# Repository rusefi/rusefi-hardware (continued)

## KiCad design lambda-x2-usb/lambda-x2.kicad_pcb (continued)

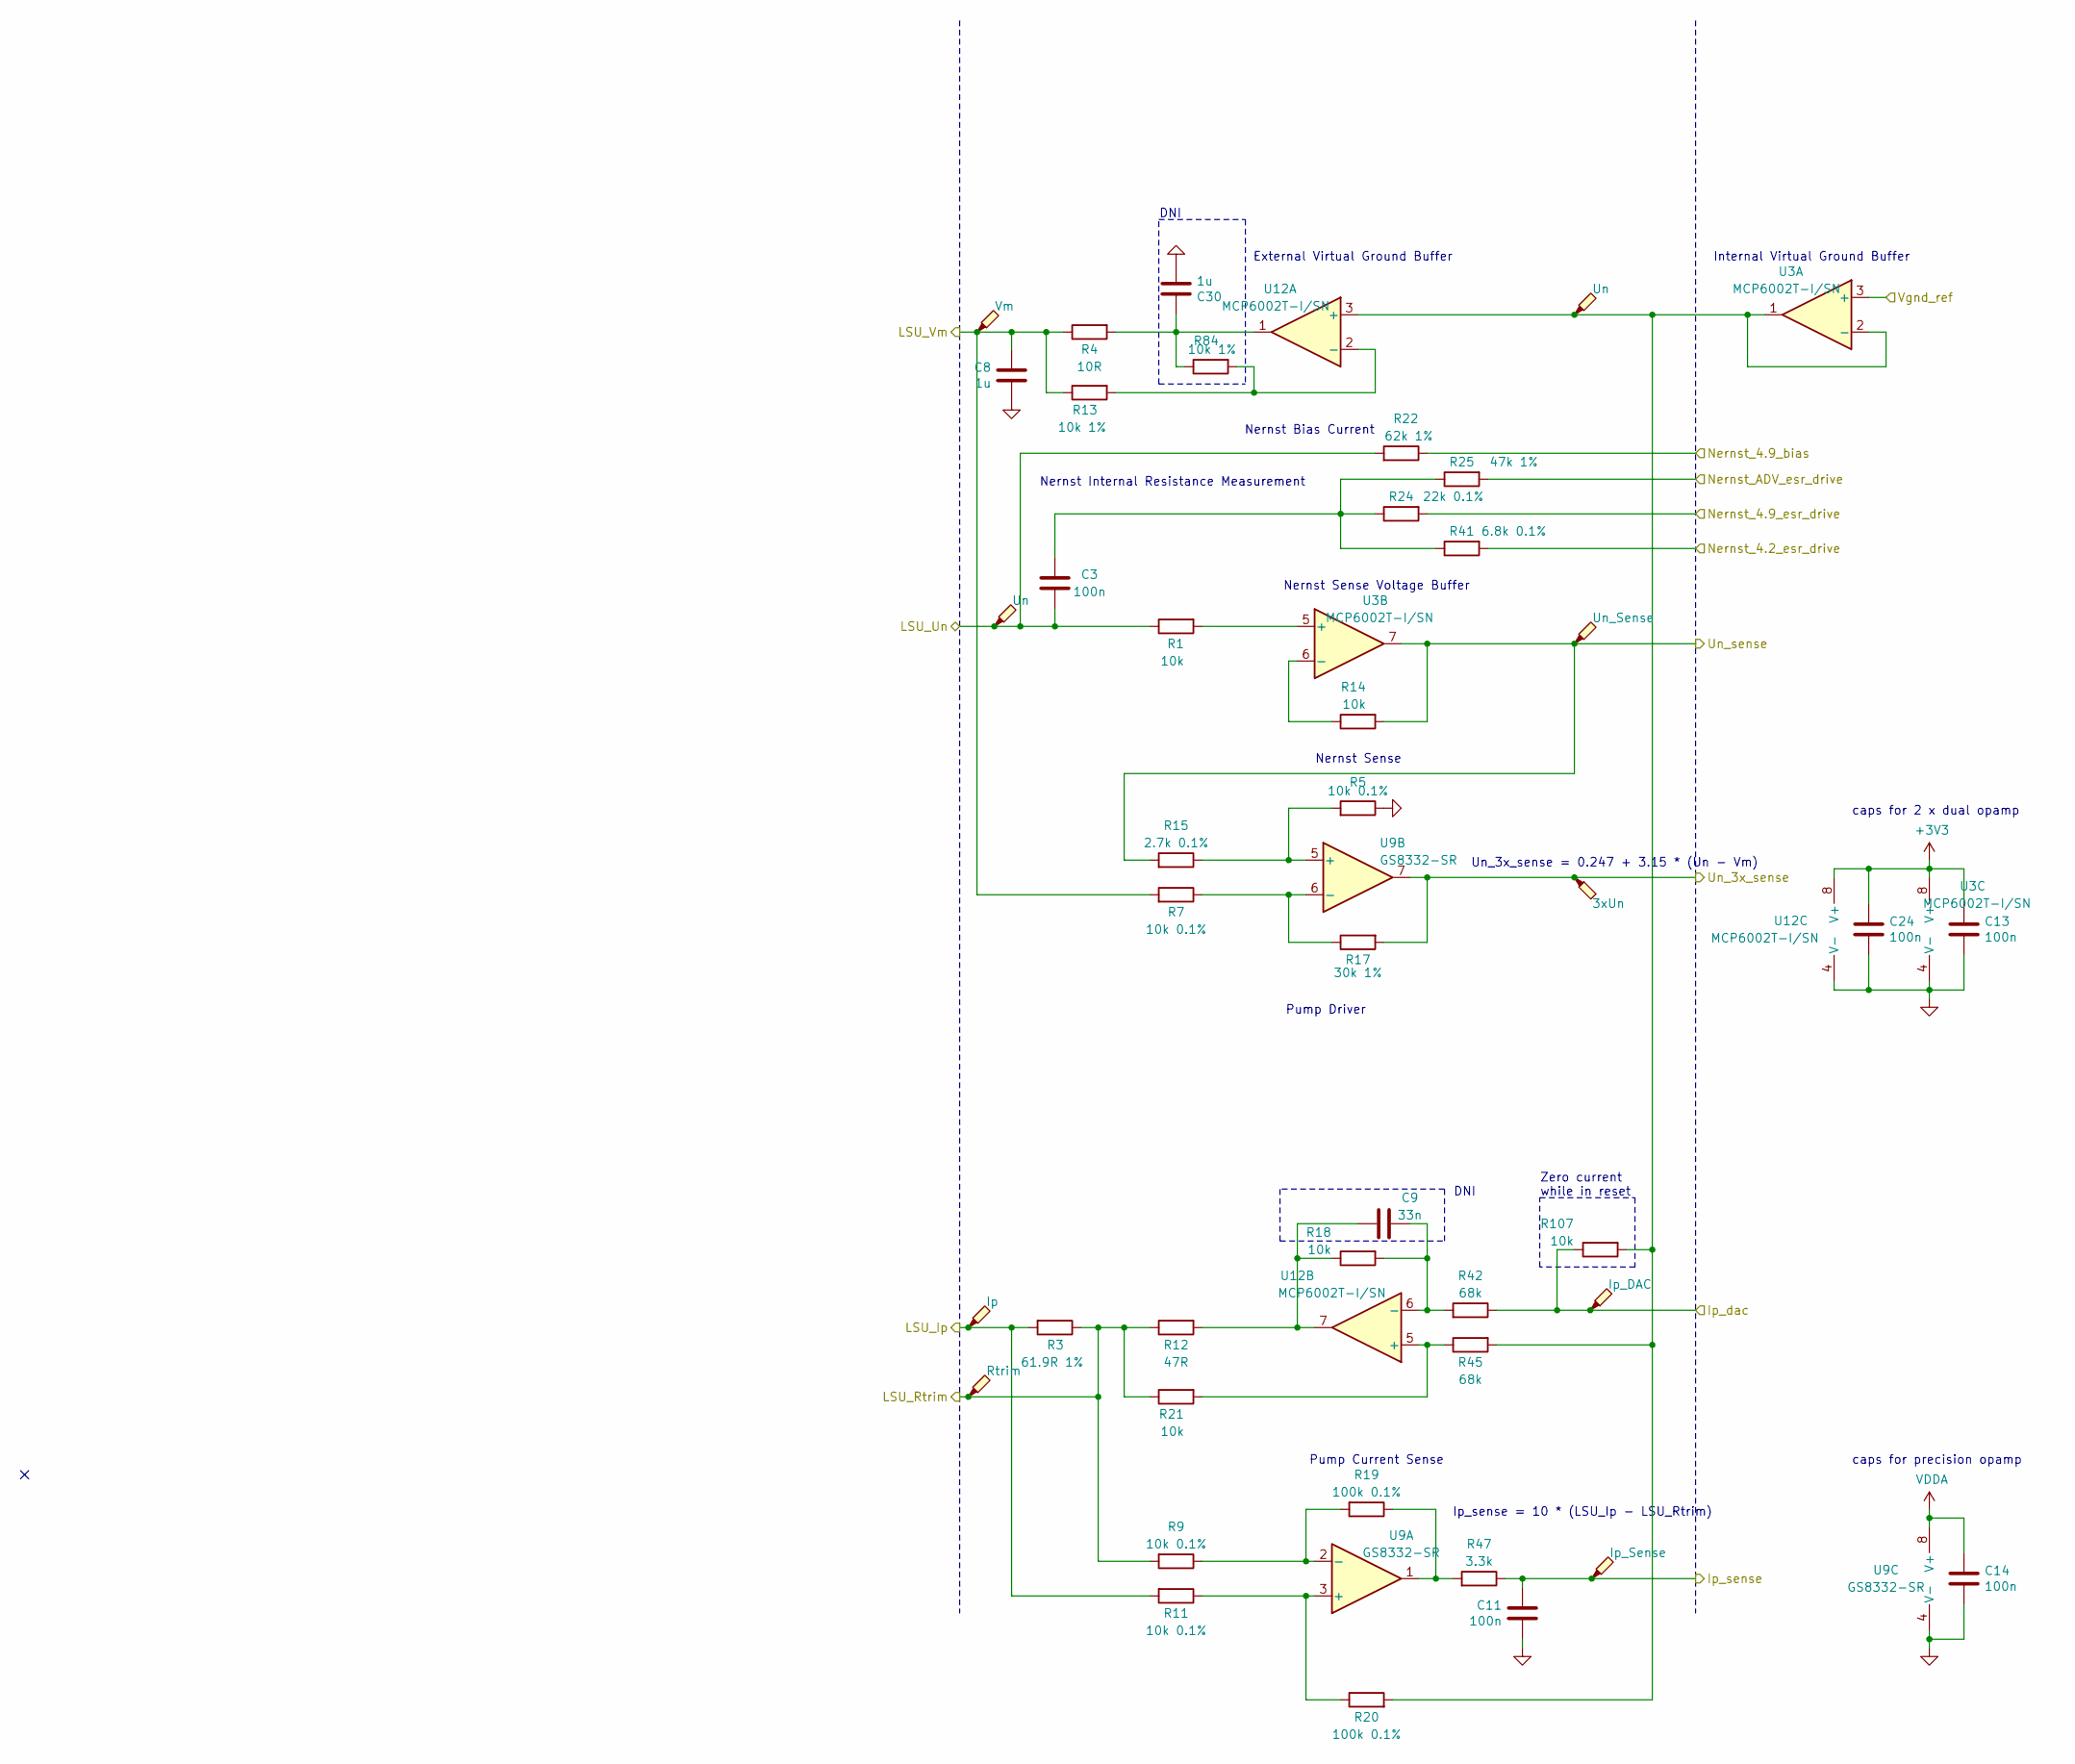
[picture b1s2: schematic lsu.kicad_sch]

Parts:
C3, C11, C13, C14, C24: 100n; C_0402_1005Metric; LCSC C1525
C8, C30: 1u; C_0402_1005Metric; LCSC C52923
C9: 33n; C_0402_1005Metric; LCSC C1585
R1, R14, R18, R21, R107: 10k; R_0402_1005Metric; LCSC C25744
R3: 61.9R 1%; R_0805_2012Metric; LCSC C322537
R4: 10R; R_1206_3216Metric; LCSC C17903
R5, R7, R9, R11: 10k 0.1%; R_0603_1608Metric; LCSC C309083
R12: 47R; R_0603_1608Metric; LCSC C328363
R13, R84: 10k 1%; R_0402_1005Metric; LCSC C25744
R15: 2.7k 0.1%; R_0603_1608Metric; LCSC C318131
R17: 30k 1%; R_0603_1608Metric; LCSC C22984
R19, R20: 100k 0.1%; R_0603_1608Metric; LCSC C122538
R22: 62k 1%; R_0603_1608Metric; LCSC C23221
R24: 22k 0.1%; R_0603_1608Metric; LCSC C705830
R25: 47k 1%; R_0603_1608Metric; LCSC C25819
R41: 6.8k 0.1%; R_0603_1608Metric; LCSC C705876
R42, R45: 68k; R_0402_1005Metric; LCSC C36871
R47: 3.3k; R_0402_1005Metric; LCSC C25890
TP3: Un_Sense; TestPoint_Pad_D1.0mm
TP5: 3xUn; TestPoint_Pad_D1.0mm
TP10: Ip; TestPoint_Pad_D1.0mm
TP11: Rtrim; TestPoint_Pad_D1.0mm
TP12: Vm; TestPoint_Pad_D1.0mm
TP13, TP14: Un; TestPoint_Pad_D1.0mm
TP15: Ip_DAC; TestPoint_Pad_D1.0mm
TP16: Ip_Sense; TestPoint_Pad_D1.0mm
U3, U12: MCP6002T-I/SN; SOIC-8_3.9x4.9mm_P1.27mm; LCSC C7377
U9: GS8332-SR; SOIC-8_3.9x4.9mm_P1.27mm; LCSC C157713

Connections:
+3V3: C13.1, C24.1, U3.8 (V+), U12.8 (V+); also elsewhere on the board
/LSU analog left/Un_sense: R14.2, R15.2, TP3.1, U3.7; also elsewhere on the board
/LSU analog left/Vgnd_ref: U3.3 (+); also elsewhere on the board
/L_Ip_dac: R42.1, R107.1, TP15.1; also elsewhere on the board
/L_Ip_sense: C11.1, R47.1, TP16.1; also elsewhere on the board
/L_LSU_Ip: R3.2, R11.2, TP10.1; also elsewhere on the board
/L_LSU_Rtrim: R3.1, R9.2, R12.1, R21.1, TP11.1; also elsewhere on the board
/L_LSU_Un: C3.1, R1.1, R22.2, TP13.1; also elsewhere on the board
/L_LSU_Vm: C8.1, R4.1, R7.2, R13.1, TP12.1; also elsewhere on the board
/L_Nernst_4.2_esr_drive: R41.2; also elsewhere on the board
/L_Nernst_4.9_bias: R22.1; also elsewhere on the board
/L_Nernst_4.9_esr_drive: R24.2; also elsewhere on the board
/L_Nernst_ADV_esr_drive: R25.2; also elsewhere on the board
/L_Un_3x_sense: R17.2, TP5.1, U9.7; also elsewhere on the board
GND: C8.2, C11.2, C13.2, C14.2, C24.2, C30.2, R5.1, U3.4 (V-), U9.4 (V-), U12.4 (V-); also elsewhere on the board
unnamed: C3.2, R24.1, R25.1, R41.1
unnamed: C9.1, R12.2, R18.1, U12.7
unnamed: C30.1, R4.2, R84.1, U12.1
unnamed: R19.1, R47.2, U9.1
unnamed: R1.2, U3.5 (+)
unnamed: R14.1, U3.6 (-)
unnamed: R11.1, R20.1, U9.3 (+)
unnamed: R9.1, R19.2, U9.2 (-)
unnamed: R5.2, R15.1, U9.5 (+)
unnamed: R7.1, R17.1, U9.6 (-)
unnamed: R20.2, R45.2, R107.2, TP14.1, U3.1, U3.2 (-), U12.3 (+)
unnamed: R13.2, R84.2, U12.2 (-)
unnamed: R21.2, R45.1, U12.5 (+)
unnamed: C9.2, R18.2, R42.2, U12.6 (-)
VDDA: C14.1, U9.8 (V+); also elsewhere on the board

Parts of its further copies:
C15, C18, C20, C23, C29: 100n; C_0402_1005Metric; LCSC C1525
C16, C31: 1u; C_0402_1005Metric; LCSC C52923
C17: 33n; C_0402_1005Metric; LCSC C1585
R54, R63, R66, R69, R108: 10k; R_0402_1005Metric; LCSC C25744
R55: 61.9R 1%; R_0805_2012Metric; LCSC C322537
R56: 10R; R_1206_3216Metric; LCSC C17903
R57, R58, R59, R60: 10k 0.1%; R_0603_1608Metric; LCSC C309083
R61: 47R; R_0603_1608Metric; LCSC C328363
R62, R85: 10k 1%; R_0402_1005Metric; LCSC C25744
R64: 2.7k 0.1%; R_0603_1608Metric; LCSC C318131
R65: 30k 1%; R_0603_1608Metric; LCSC C22984
R67, R68: 100k 0.1%; R_0603_1608Metric; LCSC C122538
R70: 62k 1%; R_0603_1608Metric; LCSC C23221
R71: 22k 0.1%; R_0603_1608Metric; LCSC C705830
R72: 47k 1%; R_0603_1608Metric; LCSC C25819
R73: 6.8k 0.1%; R_0603_1608Metric; LCSC C705876
R74, R75: 68k; R_0402_1005Metric; LCSC C36871
R77: 3.3k; R_0402_1005Metric; LCSC C25890
TP4: Un_Sense; TestPoint_Pad_D1.0mm
TP6: 3xUn; TestPoint_Pad_D1.0mm
TP17: Ip; TestPoint_Pad_D1.0mm
TP18: Rtrim; TestPoint_Pad_D1.0mm
TP19: Vm; TestPoint_Pad_D1.0mm
TP20, TP21: Un; TestPoint_Pad_D1.0mm
TP22: Ip_DAC; TestPoint_Pad_D1.0mm
TP23: Ip_Sense; TestPoint_Pad_D1.0mm
U10, U13: MCP6002T-I/SN; SOIC-8_3.9x4.9mm_P1.27mm; LCSC C7377
U11: GS8332-SR; SOIC-8_3.9x4.9mm_P1.27mm; LCSC C157713

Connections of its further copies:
+3V3: C20.1, C29.1, U10.8 (V+), U13.8 (V+); also elsewhere on the board
/LSU analog left/Vgnd_ref: U10.3 (+); also elsewhere on the board
/LSU analog right/Un_sense: R63.2, R64.2, TP4.1, U10.7; also elsewhere on the board
/R_Ip_dac: R74.1, R108.1, TP22.1; also elsewhere on the board
/R_Ip_sense: C18.1, R77.1, TP23.1; also elsewhere on the board
/R_LSU_Ip: R55.2, R60.2, TP17.1; also elsewhere on the board
/R_LSU_Rtrim: R55.1, R59.2, R61.1, R69.1, TP18.1; also elsewhere on the board
/R_LSU_Un: C15.1, R54.1, R70.2, TP20.1; also elsewhere on the board
/R_LSU_Vm: C16.1, R56.1, R58.2, R62.1, TP19.1; also elsewhere on the board
/R_Nernst_4.2_esr_drive: R73.2; also elsewhere on the board
/R_Nernst_4.9_bias: R70.1; also elsewhere on the board
/R_Nernst_4.9_esr_drive: R71.2; also elsewhere on the board
/R_Nernst_ADV_esr_drive: R72.2; also elsewhere on the board
/R_Un_3x_sense: R65.2, TP6.1, U11.7; also elsewhere on the board
GND: C16.2, C18.2, C20.2, C23.2, C29.2, C31.2, R57.1, U10.4 (V-), U11.4 (V-), U13.4 (V-); also elsewhere on the board
unnamed: C15.2, R71.1, R72.1, R73.1
unnamed: C17.1, R61.2, R66.1, U13.7
unnamed: C31.1, R56.2, R85.1, U13.1
unnamed: R67.1, R77.2, U11.1
unnamed: R68.2, R75.2, R108.2, TP21.1, U10.1, U10.2 (-), U13.3 (+)
unnamed: R54.2, U10.5 (+)
unnamed: R63.1, U10.6 (-)
unnamed: R60.1, R68.1, U11.3 (+)
unnamed: R59.1, R67.2, U11.2 (-)
unnamed: R57.2, R64.1, U11.5 (+)
unnamed: R58.1, R65.1, U11.6 (-)
unnamed: R62.2, R85.2, U13.2 (-)
unnamed: R69.2, R75.1, U13.5 (+)
unnamed: C17.2, R66.2, R74.2, U13.6 (-)
VDDA: C23.1, U11.8 (V+); also elsewhere on the board

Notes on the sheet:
Nernst Sense Voltage Buffer
Ip_sense = 10 * (LSU_Ip - LSU_Rtrim)
caps for 2 x dual opamp
Nernst Sense
Nernst Bias Current
DNI
Pump Current Sense
External Virtual Ground Buffer
Internal Virtual Ground Buffer
Un_3x_sense = 0.247 + 3.15 * (Un - Vm)
Pump Driver
Nernst Internal Resistance Measurement
Zero current while in reset
caps for precision opamp

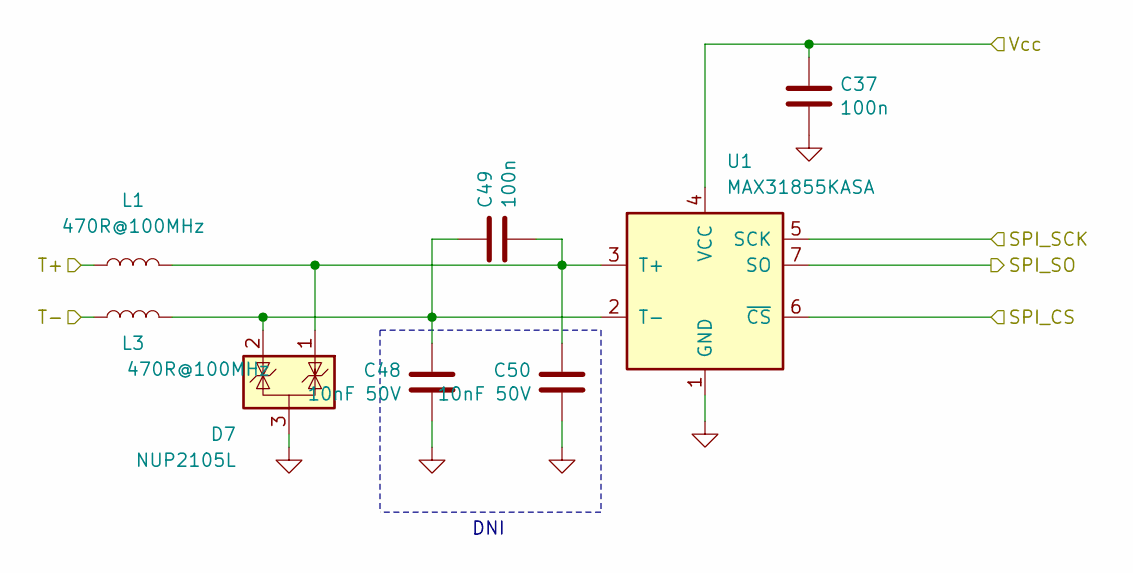
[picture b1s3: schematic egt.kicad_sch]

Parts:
C37, C49: 100n; C_0402_1005Metric; LCSC C1525
C48, C50: 10nF 50V; C_0402_1005Metric; LCSC C1524
D7: NUP2105L; SOT-23; LCSC C284104
L1, L3: 470R@100MHz; L_0603_1608Metric; LCSC C97853
U1: MAX31855KASA; SOIC-8_3.9x4.9mm_P1.27mm; LCSC C52028

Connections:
+3V3: C37.1, U1.4 (VCC); also elsewhere on the board
/L_EGT+: L1.1; also elsewhere on the board
/L_EGT-: L3.1; also elsewhere on the board
/SPI1_CS0: U1.6 (~CS); also elsewhere on the board
/SPI1_MISO: U1.7 (SO); also elsewhere on the board
/SPI1_SCK: U1.5 (SCK); also elsewhere on the board
GND: C37.2, C48.2, C50.2, D7.3 (A), U1.1 (GND); also elsewhere on the board
unnamed: C49.2, C50.1, D7.1 (K), L1.2, U1.3 (T+)
unnamed: C48.1, C49.1, D7.2 (K), L3.2, U1.2 (T-)

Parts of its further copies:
C12, C51, C53, C58, C61, C63, C66, C68, C76, C82, C85, C87, C90, C92: 10nF 50V; C_0402_1005Metric; LCSC C1524
C19, C46, C52, C59, C62, C64, C67, C69, C81, C83, C86, C88, C91, C93: 100n; C_0402_1005Metric; LCSC C1525
D9, D10, D11, D13, D14, D15, D16: NUP2105L; SOT-23; LCSC C284104
L2, L4, L6, L7, L8, L9, L10, L11, L12, L13, L14, L15, L16, L17: 470R@100MHz; L_0603_1608Metric; LCSC C97853
U14, U15, U16, U18, U19, U20, U21: MAX31855KASA; SOIC-8_3.9x4.9mm_P1.27mm; LCSC C52028

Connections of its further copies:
+3V3: C46.1, C59.1, C64.1, C69.1, C83.1, C88.1, C93.1, U14.4 (VCC), U15.4 (VCC), U16.4 (VCC), U18.4 (VCC), U19.4 (VCC), U20.4 (VCC), U21.4 (VCC); also elsewhere on the board
/L2_EGT+: L6.1; also elsewhere on the board
/L2_EGT-: L7.1; also elsewhere on the board
/L3_EGT+: L8.1; also elsewhere on the board
/L3_EGT-: L9.1; also elsewhere on the board
/L4_EGT+: L10.1; also elsewhere on the board
/L4_EGT-: L11.1; also elsewhere on the board
/R2_EGT+: L12.1; also elsewhere on the board
/R2_EGT-: L13.1; also elsewhere on the board
/R3_EGT+: L14.1; also elsewhere on the board
/R3_EGT-: L15.1; also elsewhere on the board
/R4_EGT+: L16.1; also elsewhere on the board
/R4_EGT-: L17.1; also elsewhere on the board
/R_EGT+: L2.1; also elsewhere on the board
/R_EGT-: L4.1; also elsewhere on the board
/SPI1_CS1: U14.6 (~CS); also elsewhere on the board
/SPI1_CS2: U15.6 (~CS); also elsewhere on the board
/SPI1_CS3: U19.6 (~CS); also elsewhere on the board
/SPI1_CS4: U16.6 (~CS); also elsewhere on the board
/SPI1_CS5: U20.6 (~CS); also elsewhere on the board
/SPI1_CS6: U18.6 (~CS); also elsewhere on the board
/SPI1_CS7: U21.6 (~CS); also elsewhere on the board
/SPI1_MISO: U14.7 (SO), U15.7 (SO), U16.7 (SO), U18.7 (SO), U19.7 (SO), U20.7 (SO), U21.7 (SO); also elsewhere on the board
/SPI1_SCK: U14.5 (SCK), U15.5 (SCK), U16.5 (SCK), U18.5 (SCK), U19.5 (SCK), U20.5 (SCK), U21.5 (SCK); also elsewhere on the board
GND: C12.2, C46.2, C51.2, C53.2, C58.2, C59.2, C61.2, C63.2, C64.2, C66.2, C68.2, C69.2, C76.2, C82.2, C83.2, C85.2, C87.2, C88.2, C90.2, C92.2, C93.2, D9.3 (A), D10.3 (A), D11.3 (A), D13.3 (A), D14.3 (A), D15.3 (A), D16.3 (A), U14.1 (GND), U15.1 (GND), U16.1 (GND), U18.1 (GND), U19.1 (GND), U20.1 (GND), U21.1 (GND); also elsewhere on the board
unnamed: C52.2, C53.1, D9.1 (K), L2.2, U14.3 (T+)
unnamed: C51.1, C52.1, D9.2 (K), L4.2, U14.2 (T-)
unnamed: C19.2, C58.1, D10.1 (K), L6.2, U15.3 (T+)
unnamed: C12.1, C19.1, D10.2 (K), L7.2, U15.2 (T-)
unnamed: C62.2, C63.1, D11.1 (K), L8.2, U16.3 (T+)
unnamed: C61.1, C62.1, D11.2 (K), L9.2, U16.2 (T-)
unnamed: C67.2, C68.1, D13.1 (K), L10.2, U18.3 (T+)
unnamed: C66.1, C67.1, D13.2 (K), L11.2, U18.2 (T-)
unnamed: C81.2, C82.1, D14.1 (K), L12.2, U19.3 (T+)
unnamed: C76.1, C81.1, D14.2 (K), L13.2, U19.2 (T-)
unnamed: C86.2, C87.1, D15.1 (K), L14.2, U20.3 (T+)
unnamed: C85.1, C86.1, D15.2 (K), L15.2, U20.2 (T-)
unnamed: C91.2, C92.1, D16.1 (K), L16.2, U21.3 (T+)
unnamed: C90.1, C91.1, D16.2 (K), L17.2, U21.2 (T-)

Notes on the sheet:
DNI

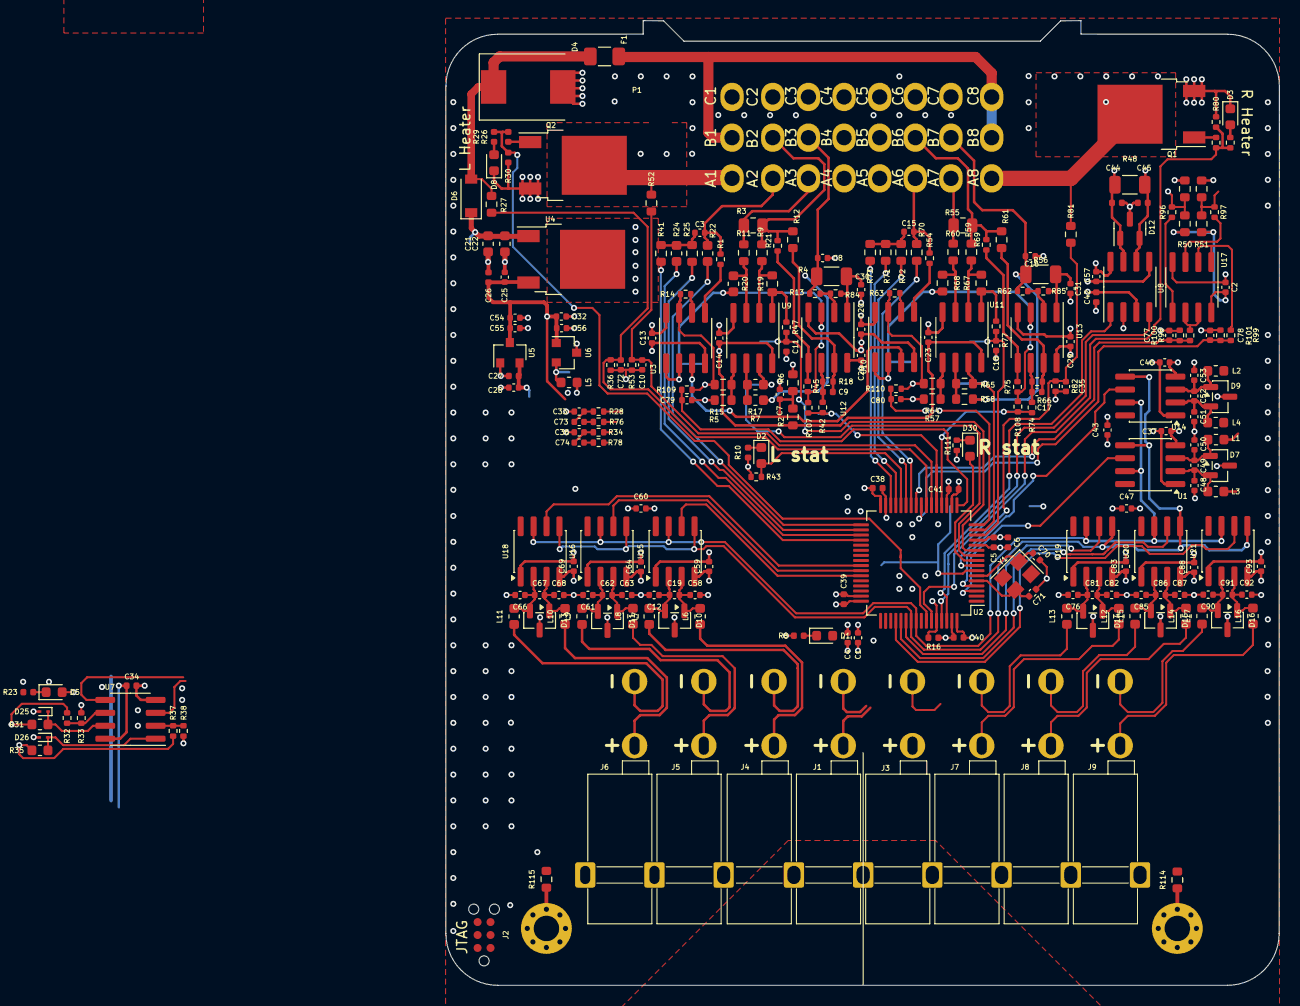
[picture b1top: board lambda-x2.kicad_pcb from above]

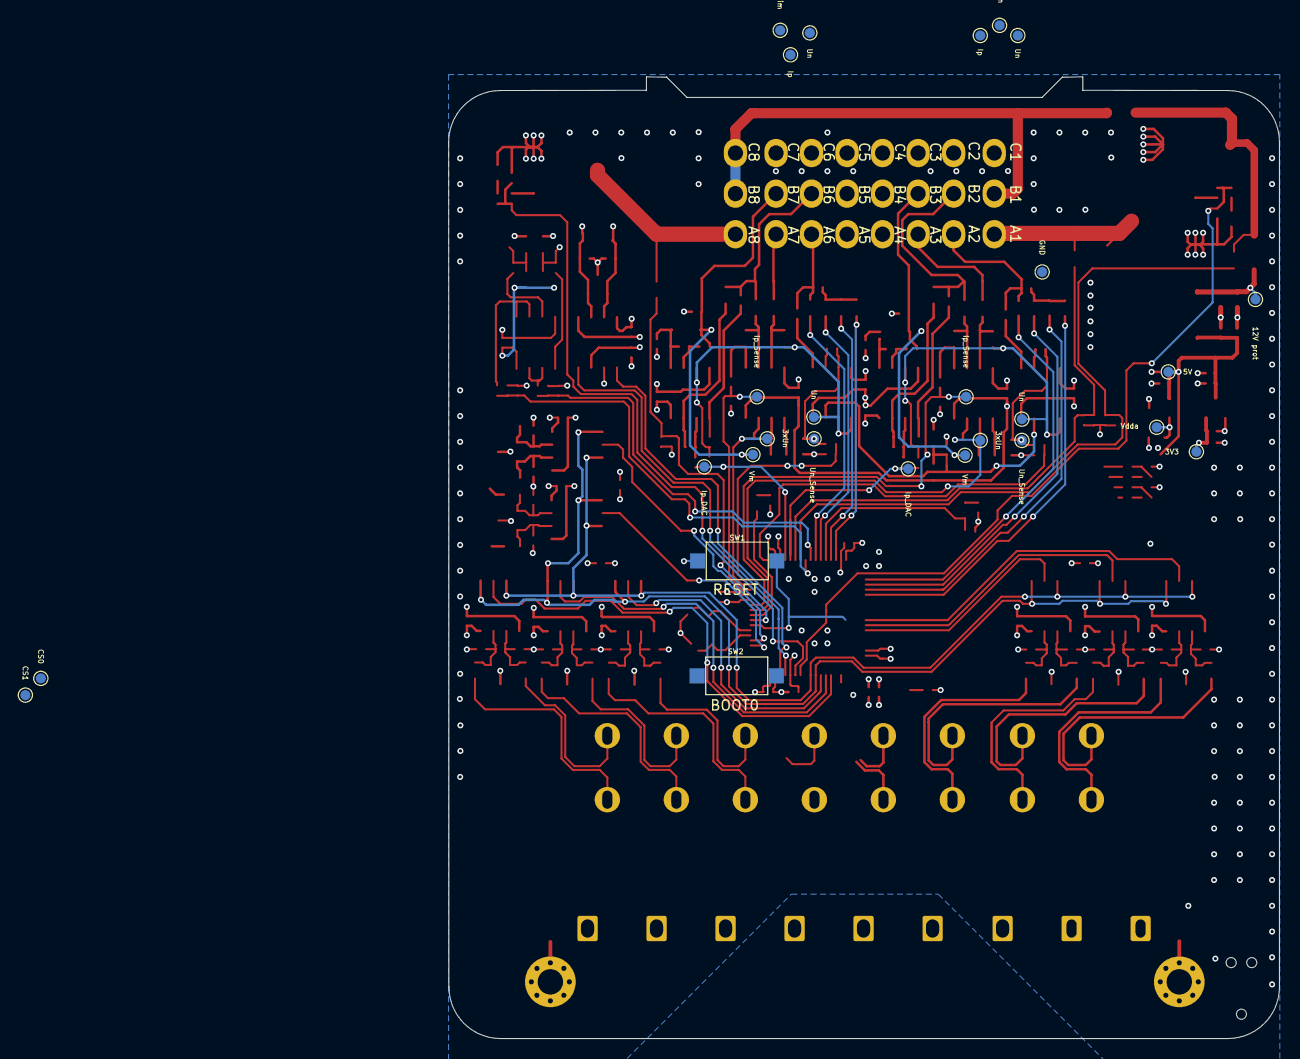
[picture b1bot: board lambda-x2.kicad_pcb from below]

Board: 4 copper layers, 81.9 x 94.8 mm, 284 parts (27 on the bottom side), 156 nets.

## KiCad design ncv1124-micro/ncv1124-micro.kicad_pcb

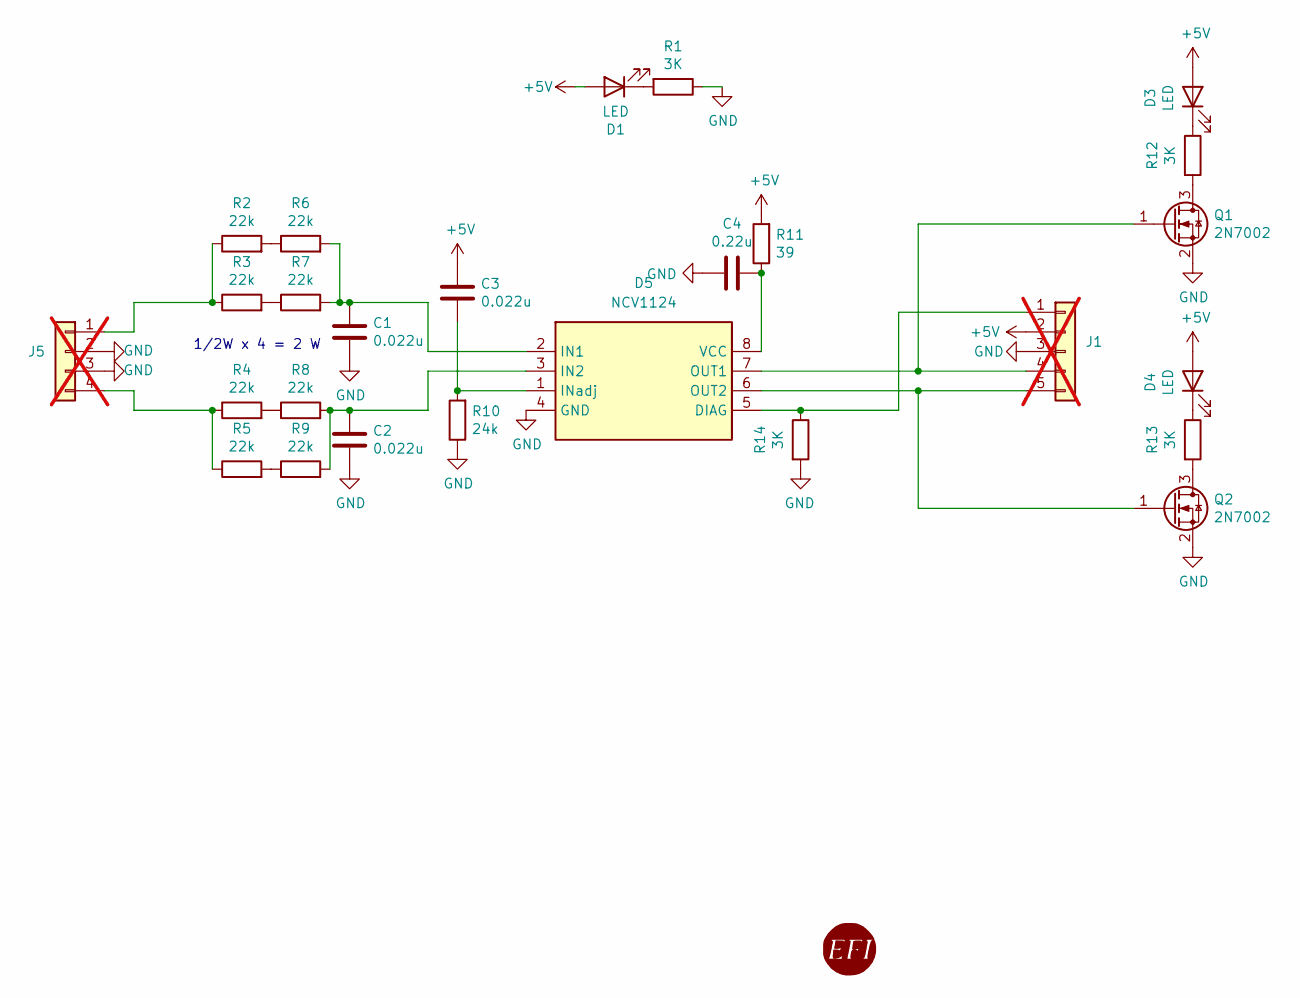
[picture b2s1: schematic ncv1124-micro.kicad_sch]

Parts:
C1, C2, C3: 0.022u; C_0603_1608Metric; LCSC C21122
C4: 0.22u; C_0603_1608Metric; LCSC C21120
D1, D3, D4: LED; LED_0603_1608Metric; LCSC C2290
D5: NCV1124; SO-8_3.9x4.9mm_P1.27mm; LCSC C152274
G1: RUSEFI_LOGO; rusefi_logo
J1: Conn_01x05; PinHeader_1x05_P2.54mm_Vertical; not fitted
J5: Conn_01x04; PinHeader_1x04_P2.54mm_Vertical; not fitted
Q1, Q2: 2N7002; SOT-23; LCSC C8545
R1, R12, R13, R14: 3K; R_0603_1608Metric; LCSC C4211
R2, R3, R4, R5, R6, R7, R8, R9: 22k; R_1210_3225Metric_Pad1.30x2.65mm_HandSolder; LCSC C230119
R10: 24k; R_0603_1608Metric; LCSC C23352
R11: 39; R_0603_1608Metric; LCSC C23154

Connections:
+5V: C3.1, D1.2 (A), D3.2 (A), D4.2 (A), J1.2, R11.2
GND: C1.2, C2.2, C4.2, D5.4 (GND), J1.3, J5.2, J5.3, Q1.2 (S), Q2.2 (S), R1.1, R10.1, R14.2
unnamed: D1.1 (K), R1.2
unnamed: D3.1 (K), R12.1
unnamed: D4.1 (K), R13.1
unnamed: D5.5 (DIAG), J1.1, R14.1
unnamed: C1.1, D5.2 (IN1), R6.2, R7.2
unnamed: C2.1, D5.3 (IN2), R8.2, R9.2
unnamed: C3.2, D5.1 (INadj), R10.2
unnamed: D5.7 (OUT1), J1.4, Q1.1 (G)
unnamed: D5.6 (OUT2), J1.5, Q2.1 (G)
unnamed: C4.1, D5.8 (VCC), R11.1
unnamed: J5.1, R2.1, R3.1
unnamed: J5.4, R4.1, R5.1
unnamed: Q1.3 (D), R12.2
unnamed: Q2.3 (D), R13.2
unnamed: R2.2, R6.1
unnamed: R3.2, R7.1
unnamed: R4.2, R8.1
unnamed: R5.2, R9.1

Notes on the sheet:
1/2W x 4 = 2 W

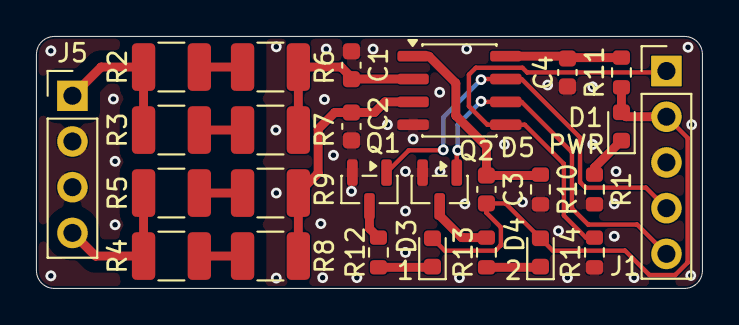
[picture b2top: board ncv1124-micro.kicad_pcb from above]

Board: 2 copper layers, 37.0 x 14.0 mm, 27 parts (1 on the bottom side), 20 nets.

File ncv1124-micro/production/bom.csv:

Designator,Footprint,Quantity,Value,LCSC Part #
"C1, C2, C3",0603,3,0.022u,C21122
C4,0603,1,0.22u,C21120
"D1, D3, D4",0603,3,LED,C2290
D5,SO-8_3.9x4.9mm_P1.27mm,1,NCV1124,C152274
"Q1, Q2",SOT-23,2,2N7002,C8545
"R1, R12, R13, R14",0603,4,3K,C4211
R10,0603,1,24k,C23352
R11,0603,1,39,C23154
"R2, R3, R4, R5, R6, R7, R8, R9",1210,8,22k,C230119

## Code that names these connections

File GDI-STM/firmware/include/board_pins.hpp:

#ifndef BOARD_PINS_HPP
#define BOARD_PINS_HPP

#include "stm32g4xx_hal.h"

#include <cstddef>
#include <cstdint>

namespace board {

struct GpioPin {
    GPIO_TypeDef* port;
    uint16_t pin;
};

// From `GDI-STM.kicad_pcb` (U7: STM32G474M, LQFP-80) - produced PCB is source of truth.
inline constexpr size_t kNumInjectors = 8;

// INJ1..INJ8 -> PE8..PE15 (LQFP80 pins 31..38).
inline constexpr GpioPin kInjPins[kNumInjectors] = {
    {GPIOE, GPIO_PIN_8},  // INJ1
    {GPIOE, GPIO_PIN_9},  // INJ2
    {GPIOE, GPIO_PIN_10}, // INJ3
    {GPIOE, GPIO_PIN_11}, // INJ4
    {GPIOE, GPIO_PIN_12}, // INJ5
    {GPIOE, GPIO_PIN_13}, // INJ6
    {GPIOE, GPIO_PIN_14}, // INJ7
    {GPIOE, GPIO_PIN_15}, // INJ8
};

// START1..START8 -> PA9,PA10,PB3,PB4,PA15,PB5,PB6,PB9 (pins 57,58,72,73,65,74,75,78).
inline constexpr GpioPin kStartPins[kNumInjectors] = {
    {GPIOA, GPIO_PIN_9},  // START1
    {GPIOA, GPIO_PIN_10}, // START2
    {GPIOB, GPIO_PIN_3},  // START3
    {GPIOB, GPIO_PIN_4},  // START4
    {GPIOA, GPIO_PIN_15}, // START5
    {GPIOB, GPIO_PIN_5},  // START6
    {GPIOB, GPIO_PIN_6},  // START7
    {GPIOB, GPIO_PIN_9},  // START8
};

// FDCAN1: CAN_TX -> PA12 (pin 60), CAN_RX -> PA11 (pin 59).
inline constexpr GpioPin kCanTx = {GPIOA, GPIO_PIN_12}; // CAN_TX
inline constexpr GpioPin kCanRx = {GPIOA, GPIO_PIN_11}; // CAN_RX

// High-side sense/control nets
// From `bank.kicad_sch` these nets feed IRS21867S gate-driver inputs (HIN). The firmware treats them as
// digital control outputs and holds them LOW at boot for safety (drivers disabled).
inline constexpr GpioPin kHsVbat[4] = {
    {GPIOC, GPIO_PIN_6}, // HS_VBAT1 (pin 52)
    {GPIOC, GPIO_PIN_7}, // HS_VBAT2 (pin 53)
    {GPIOC, GPIO_PIN_8}, // HS_VBAT3 (pin 54)
    {GPIOC, GPIO_PIN_9}, // HS_VBAT4 (pin 55)
};

inline constexpr GpioPin kHsVboost[4] = {
    {GPIOC, GPIO_PIN_10}, // HS_VBOOST1 (pin 66)
    {GPIOC, GPIO_PIN_11}, // HS_VBOOST2 (pin 67)
    {GPIOC, GPIO_PIN_12}, // HS_VBOOST3 (pin 68)
    {GPIOC, GPIO_PIN_13}, // HS_VBOOST4 (pin 2)
};

// Boost driver PWM/control.
inline constexpr GpioPin kBoostPwm = {GPIOD, GPIO_PIN_0}; // BOOST_PWM (pin 69)

// Analog sense pins (configured as analog inputs by board init).
inline constexpr GpioPin kSenseVboost = {GPIOE, GPIO_PIN_7};   // Vboost (pin 30)
inline constexpr GpioPin kSenseVoboost = {GPIOA, GPIO_PIN_8};  // Voboost (pin 56)
inline constexpr GpioPin kSenseVo1 = {GPIOA, GPIO_PIN_2};      // Vo1 (pin 14)
inline constexpr GpioPin kSenseVo2 = {GPIOA, GPIO_PIN_6};      // Vo2 (pin 20)
inline constexpr GpioPin kSenseVo3 = {GPIOB, GPIO_PIN_1};      // Vo3 (pin 25)
inline constexpr GpioPin kSenseVo4 = {GPIOB, GPIO_PIN_12};     // Vo4 (pin 43)

inline constexpr GpioPin kSenseVinM1 = {GPIOC, GPIO_PIN_5};     // VinM1 (pin 23)
inline constexpr GpioPin kSenseVinM2 = {GPIOA, GPIO_PIN_5};     // VinM2 (pin 19)
inline constexpr GpioPin kSenseVinM3 = {GPIOB, GPIO_PIN_2};     // VinM3 (pin 26)
inline constexpr GpioPin kSenseVinM4 = {GPIOB, GPIO_PIN_10};    // VinM4 (pin 39)
inline constexpr GpioPin kSenseVinMboost = {GPIOB, GPIO_PIN_15}; // VinMboost (pin 46)

inline constexpr GpioPin kSenseVinP1 = {GPIOA, GPIO_PIN_7};      // VinP1 (pin 21)
inline constexpr GpioPin kSenseVinP2 = {GPIOB, GPIO_PIN_0};      // VinP2 (pin 24)
inline constexpr GpioPin kSenseVinP3 = {GPIOB, GPIO_PIN_13};     // VinP3 (pin 44)
inline constexpr GpioPin kSenseVinP4 = {GPIOB, GPIO_PIN_11};     // VinP4 (pin 42)
inline constexpr GpioPin kSenseVinPboost = {GPIOC, GPIO_PIN_3};  // VinPboost (pin 11)

inline constexpr GpioPin kSenseVinj1 = {GPIOC, GPIO_PIN_0}; // Vinj1 (pin 8)
inline constexpr GpioPin kSenseVinj2 = {GPIOC, GPIO_PIN_1}; // Vinj2 (pin 9)
inline constexpr GpioPin kSenseVinj3 = {GPIOC, GPIO_PIN_2}; // Vinj3 (pin 10)
inline constexpr GpioPin kSenseVinj4 = {GPIOA, GPIO_PIN_0}; // Vinj4 (pin 12)
inline constexpr GpioPin kSenseVinj5 = {GPIOA, GPIO_PIN_1}; // Vinj5 (pin 13)
inline constexpr GpioPin kSenseVinj6 = {GPIOA, GPIO_PIN_3}; // Vinj6 (pin 17)
inline constexpr GpioPin kSenseVinj7 = {GPIOA, GPIO_PIN_4}; // Vinj7 (pin 18)
inline constexpr GpioPin kSenseVinj8 = {GPIOC, GPIO_PIN_4}; // Vinj8 (pin 22)

} // namespace board

#endif // BOARD_PINS_HPP

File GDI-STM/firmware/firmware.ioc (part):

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Mcu.Name=STM32G474M(B-C-E)Tx
Mcu.Package=LQFP80
Mcu.UserName=STM32G474METx
PA0.Mode=IN1-Single-Ended
PA0.Signal=ADC1_IN1
PA1.Mode=IN2-Single-Ended
PA1.Signal=ADC1_IN2
PA11.Mode=FDCAN_Activate
PA11.Signal=FDCAN1_RX
PA12.Mode=FDCAN_Activate
PA12.Signal=FDCAN1_TX
PA13.Mode=Serial_Wire
PA13.Signal=SYS_JTMS-SWDIO
PA14.Mode=Serial_Wire
PA14.Signal=SYS_JTCK-SWCLK
PA2.Mode=Standalone
PA2.Signal=OPAMP1_VOUT
PA3.Mode=IN4-Single-Ended
PA3.Signal=ADC1_IN4
PA4.Mode=IN17-Single-Ended
PA4.Signal=ADC2_IN17
PA5.Mode=Standalone
PA5.Signal=OPAMP2_VINM
PA6.Mode=Standalone
PA6.Signal=OPAMP2_VOUT
PA7.Mode=Standalone
PA7.Signal=OPAMP1_VINP
PA8.Mode=Standalone
PA8.Signal=OPAMP5_VOUT
PB0.Mode=Standalone
PB0.Signal=OPAMP2_VINP
PB1.Mode=Standalone
PB1.Signal=OPAMP3_VOUT
PB10.Mode=Standalone
PB10.Signal=OPAMP4_VINM
PB11.Mode=Standalone
PB11.Signal=OPAMP4_VINP
PB12.Mode=Standalone
PB12.Signal=OPAMP4_VOUT
PB13.Mode=Standalone
PB13.Signal=OPAMP3_VINP
PB14.Mode=IN5-Single-Ended
PB14.Signal=ADC1_IN5
PB15.Mode=Standalone
PB15.Signal=OPAMP5_VINM
PB2.Mode=Standalone
PB2.Signal=OPAMP3_VINM
PC0.Mode=IN6-Single-Ended
PC0.Signal=ADC1_IN6
PC1.Mode=IN7-Single-Ended
PC1.Signal=ADC1_IN7
PC2.Mode=IN8-Single-Ended
PC2.Signal=ADC1_IN8
PC3.Mode=Standalone
PC3.Signal=OPAMP5_VINP
PC4.Mode=IN5-Single-Ended
PC4.Signal=ADC2_IN5
PC5.Mode=Standalone
PC5.Signal=OPAMP1_VINM
PE13.Mode=IN3-Single-Ended
PE13.Signal=ADC3_IN3
PE7.Mode=IN4-Single-Ended
PE7.Signal=ADC3_IN4
PE9.Mode=IN2-Single-Ended
PE9.Signal=ADC3_IN2
PF0-OSC_IN.Mode=HSE-External-Oscillator
PF0-OSC_IN.Signal=RCC_OSC_IN
PF1-OSC_OUT.Mode=HSE-External-Oscillator
PF1-OSC_OUT.Signal=RCC_OSC_OUT
RCC.HSE_VALUE=20000000
RCC.SYSCLKFreq_VALUE=170000000
RCC.SYSCLKSource=RCC_SYSCLKSOURCE_PLLCLK
board=custom

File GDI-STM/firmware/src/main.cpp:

// Application entry point (STM32G474, Cortex-M4F)

#include "adc_sampler.hpp"
#include "boost_control.hpp"
#include "can_driver.hpp"
#include "gdi_can_protocol.hpp"
#include "board_init.hpp"
#include "injector_bridge.hpp"
#include "injector_control.hpp"
#include "high_side_control.hpp"
#include "safety_monitor.hpp"

#include "stm32g4xx_hal.h"

#include "FreeRTOS.h"
#include "task.h"

InjectorControl injectorControl;
InjectorBridge injectorBridge;
CanDriver canDriver;
GdiCanProtocol gdiProtocol{canDriver};
SafetyMonitor safetyMonitor;
AdcSampler adcSampler;

static void SystemClock_Config();
static void DefaultTask(void*);

extern "C" void Error_Handler(void) {
    __disable_irq();

    // Force all INJ outputs LOW (PE8-PE15).
    GPIOE->BSRR = static_cast<uint32_t>(0xFFU) << 24; // BR8..BR15
    // Force all HS enables LOW (PC6-PC13).
    GPIOC->BSRR = static_cast<uint32_t>(0xFFU) << 22; // BR6..BR13
    // Force BOOST_PWM LOW (PD0).
    GPIOD->BSRR = static_cast<uint32_t>(1U) << 16;    // BR0

    while (true) {
    }
}

int main(void) {
    HAL_Init();
    SystemClock_Config();
    board::init();

    safetyMonitor.init(&adcSampler);
    high_side::init();
    (void)injectorControl.init();
    (void)injectorBridge.init(injectorControl, safetyMonitor);
    (void)canDriver.init();
    (void)adcSampler.init();
    boost::init();

    (void)xTaskCreate(DefaultTask, "default", 512, nullptr, tskIDLE_PRIORITY + 1, nullptr);
    vTaskStartScheduler();

    // Should never reach here.
    while (true) {
    }
}

static void DefaultTask(void*) {
    for (;;) {
        safetyMonitor.checkSystemHealth();

        const bool healthy = safetyMonitor.isSystemHealthy();
        high_side::update(healthy);
        boost::update(healthy);

        adcSampler.sampleAll();

        // Process GDI CAN protocol (rusEFI)
        {
            CanMessage rxMsg;
            while (canDriver.receiveMessage(rxMsg, 0)) {
                gdiProtocol.processReceivedMessage(rxMsg);
            }
        }

        // Periodic GDI status/config transmit (~100 ms)
        gdiProtocol.periodicTransmit();

        vTaskDelay(pdMS_TO_TICKS(10));
    }
}

static void SystemClock_Config() {
    // Based on STM32CubeG4 template (STM32G474E-EVAL1):
    // System Clock source = PLL (HSI), SYSCLK/HCLK/PCLK1/PCLK2 = 170 MHz.
    RCC_ClkInitTypeDef RCC_ClkInitStruct = {0};
    RCC_OscInitTypeDef RCC_OscInitStruct = {0};

    // Enable voltage range 1 boost mode for frequency above 150 MHz.
    __HAL_RCC_PWR_CLK_ENABLE();
    (void)HAL_PWREx_ControlVoltageScaling(PWR_REGULATOR_VOLTAGE_SCALE1_BOOST);
    __HAL_RCC_PWR_CLK_DISABLE();

    // Activate PLL with HSI as source.
    RCC_OscInitStruct.OscillatorType = RCC_OSCILLATORTYPE_HSI;
    RCC_OscInitStruct.HSICalibrationValue = RCC_HSICALIBRATION_DEFAULT;
    RCC_OscInitStruct.HSIState = RCC_HSI_ON;
    RCC_OscInitStruct.PLL.PLLState = RCC_PLL_ON;
    RCC_OscInitStruct.PLL.PLLSource = RCC_PLLSOURCE_HSI;
    RCC_OscInitStruct.PLL.PLLM = RCC_PLLM_DIV4;
    RCC_OscInitStruct.PLL.PLLN = 85;
    RCC_OscInitStruct.PLL.PLLP = RCC_PLLP_DIV2;
    RCC_OscInitStruct.PLL.PLLQ = RCC_PLLQ_DIV2;
    RCC_OscInitStruct.PLL.PLLR = RCC_PLLR_DIV2;
    if (HAL_RCC_OscConfig(&RCC_OscInitStruct) != HAL_OK) {
        Error_Handler();
    }

    // Select PLL as system clock source and configure the HCLK, PCLK1 and PCLK2 clocks dividers.
    RCC_ClkInitStruct.ClockType =
        (RCC_CLOCKTYPE_SYSCLK | RCC_CLOCKTYPE_HCLK | RCC_CLOCKTYPE_PCLK1 | RCC_CLOCKTYPE_PCLK2);
    RCC_ClkInitStruct.SYSCLKSource = RCC_SYSCLKSOURCE_PLLCLK;
    RCC_ClkInitStruct.AHBCLKDivider = RCC_HCLK_DIV1;
    RCC_ClkInitStruct.APB1CLKDivider = RCC_HCLK_DIV1;
    RCC_ClkInitStruct.APB2CLKDivider = RCC_HCLK_DIV1;
    if (HAL_RCC_ClockConfig(&RCC_ClkInitStruct, FLASH_LATENCY_8) != HAL_OK) {
        Error_Handler();
    }
}
